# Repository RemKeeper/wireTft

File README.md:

# wireTFT

ESP32-WROOM-32D + ST7789 240×320 桌面屏。用低功耗蓝牙完成配网、换照片、切换方向和音乐摆件设置。控制页是静态 HTTPS 页面，浏览器通过 Web Bluetooth 直接连接设备，电脑上不用跑服务。每台设备有一个 6 位配置码，配置和控制都必须带上它，避免同一环境里的多块屏幕被误操作。

照片以 RGB565 保存在 SPIFFS 双槽中。整张图传输完并且 CRC 通过后才切换活动槽，所以断线、短包、CRC 错误都不会换掉上一张图。

硬件工程在 `hardware/`（KiCad 与嘉立创 EDA）。固件按 GPL-2.0 发布，见 `LICENSE`。

## 硬件连接

经典 ESP32、4 MB Flash、不需要 PSRAM。屏幕为 10 针 FPC 的 ST7789，无 MISO、无 TE。

| 信号 | GPIO |
|---|---|
| SCK | 18 |
| MOSI | 23 |
| CS | 21 |
| DC | 27 |
| RST | 33 |
| 背光 | 32，高电平点亮 |

SPI 时钟 40 MHz。这些引脚走 GPIO 矩阵，40 MHz 已是该路径的上限，不要改成 80 MHz，也超出 ST7789 的时钟规格。

## 控制页面

页面源码在 `web/public/`，用 Cloudflare Workers 的静态资源托管（`web/wrangler.jsonc`，没有 Worker 脚本）。需要桌面版 Chrome / Edge，或 Android Chrome。iOS Safari 没有 Web Bluetooth。

```text
cd web
npx wrangler deploy
```

部署完成后用自己的 `*.workers.dev` 地址打开：

1. 「搜索并连接蓝牙设备」，选择 `wireTFT-xxxx`（后 4 位是设备 ID 的末尾）。
2. 输入串口打印的 6 位配置码。勾选「记住」后，配置码按设备名存在这个浏览器的 localStorage。
3. 「02 Wi-Fi」扫描 2.4 GHz 网络并保存。
4. 「03 屏幕与画面」切换竖屏 / 横屏、发送图片、填写音乐服务地址。

照片和方向只需要蓝牙。音乐摆件需要设备已经连上 Wi-Fi。`_headers` 限制了脚本来源，并只允许本页使用蓝牙。

## 配置码

- NVS 里没有配置码时，用硬件随机数生成 6 位数字，存在键 `code`，之后重启不变。
- 每次启动串口都会打印配置码和蓝牙名称，格式为 `配置码：<六位数字>  蓝牙名称：wireTFT-xxxx`。串口输入 `code` 可再看一次，`code reset` 生成新码，浏览器里记住的旧码立即失效。
- 连续输错 5 次后，60 秒内拒绝所有要配置码的操作。蓝牙返回 `locked`，局域网返回 429。
- 蓝牙不配对、不加密。配置码只防止误操作，挡不住能听空口的人。Wi-Fi 密码也是明文经过空口，在可信环境里配网。

## 串口命令

115200 baud、8N1。打开串口会复位芯片（DTR/RTS）。

```text
wifi setup   # 交互式输入 SSID 与密码（密码不回显）
wifi status  # 连接状态与 IP
wifi forget  # 删除保存的凭据，回退到编译配置
code         # 显示配置码
code reset   # 重新生成配置码
wifi help    # 帮助
```

SSID 为 1–32 字节。密码可以为空（开放网络）、8–63 个可打印字符，或 64 位十六进制 PSK。蓝牙和串口写的是同一条 NVS 记录。没有这条记录时，使用 `idf.py menuconfig → wireTFT Wi-Fi` 里的编译配置。两项都空时不连接，等待蓝牙或串口配网。设备只支持 2.4 GHz。

没有照片时显示等待画面，底部有蓝牙名称和 Wi-Fi 状态（`WiFi OK <IP>` 等）。照片和音乐界面占满全屏。

## 构建与烧录

在 ESP-IDF 5.5 上验证。另外两个依赖要单独准备，本仓库不包含它们：

- [Arduino-ESP32 3.3.12](https://github.com/espressif/arduino-esp32/releases/tag/3.3.12)，用作 IDF 组件。`ARDUINO_COMPONENT_PATH` 指向里面的 `components/arduino`。
- [Arduino_GFX 1.6.3](https://github.com/moononournation/Arduino_GFX/releases/tag/1.6.3) 的源码目录。

这不是 Arduino IDE 工程。根 `CMakeLists.txt` 在两个路径为空时会直接失败。

```text
. $IDF_PATH/export.sh
idf.py -B build set-target esp32 \
  -DARDUINO_COMPONENT_PATH=/path/to/arduino \
  -DARDUINO_GFX_PATH=/path/to/Arduino_GFX-1.6.3
idf.py -B build menuconfig
idf.py -B build build
```

`menuconfig` 里的 `wireTFT Wi-Fi` 可以留空，以后用蓝牙或串口配置。如果在这里填了密码，它会写进构建目录的 `sdkconfig`。`sdkconfig` 已被忽略，不要提交，也不要把它和固件一起外发。

第一次烧录写入 bootloader、分区表和应用，按地址写入，不擦整片：

```text
idf.py -B build -p PORT -b 460800 flash
```

`PORT` 在 Linux 上一般是 `/dev/ttyUSB0`，Windows 上是 `COMx`。用 WSL 时，USB 串口要先接到这个发行版里。之后只改了应用：

```text
idf.py -B build -p PORT -b 460800 app-flash
```

`app-flash` 只覆盖 `0x10000` 的 factory 分区，下面这些会留下来：

| 分区 | 偏移 | 大小 | 内容 |
|---|---|---|---|
| nvs | `0x9000` | 24 KB | Wi-Fi、配置码、方向、音乐地址 |
| phy_init | `0xf000` | 4 KB | 分区表保留；本固件不往里写校准数据 |
| factory | `0x10000` | 2 MB | 应用程序 |
| images | `0x210000` | 1984 KB | 两张照片 |

不要运行 `idf.py erase-flash` 或 `esptool erase_flash`。那会清掉 NVS 和照片。也不要改 `partitions.csv` 之后再整片烧录，除非接受这些数据消失。NVS 初始化失败时固件直接停住，不会自动擦除 NVS。

烧录后用 115200 打开串口，确认打印了蓝牙名称和配置码：

```text
idf.py -B build -p PORT monitor
```

## 二次开发注意事项

### 单核

`sdkconfig.defaults` 打开了 `CONFIG_FREERTOS_UNICORE`。Wi-Fi、蓝牙控制器和 Arduino `loop` 都在 CPU0 上。不要为了“还有一个核”就关掉这个选项：Arduino loop、音乐任务和 NimBLE host 任务的亲和性、`displayLock`（屏幕）和 `musicLock`（快照）都是按单核来的。

同时固定的还有：

- `CONFIG_ESP32_REV_MIN_0`：二进制兼容 rev0 及以后。不要使用只有 rev3 才有的指令。
- `CONFIG_FREERTOS_HZ=1000`。
- Arduino loop 栈 8192 字节。音乐任务栈 8192 字节、优先级 1。NimBLE host 任务栈 6144 字节。

### Wi-Fi

固件不使用 Arduino 的 `WiFi.h`，由 `wifi_bridge.c` 直接调用 ESP-IDF 的 `esp_wifi`，只做 STA。`wifi_bridge_ap_start()` 是未接入主流程的热点辅助函数，正常启动不会开 AP。

- 凭据先用 NVS 里由蓝牙或串口写入的记录，否则用 menuconfig 的 `CONFIG_WIRETFT_SSID` / `CONFIG_WIRETFT_PASSWORD`。
- 断线后最多自动重连 5 次，用尽后要检查路由器并重启。
- HTTP 只绑在 STA 的私网 IPv4 80 端口。根 CMake 把 IDF 5.5 的 `httpd_main.c` 收成仅 IPv4，再用 `lwip_bind` 包装限制来源。不要改成监听所有地址，也不要做公网端口转发。
- `CONFIG_ESP_WIFI_STATIC_RX_BUFFER_NUM=6`，是为了给音乐模式留内部 RAM。调大就会挤占堆。
- `CONFIG_ESP_PHY_CALIBRATION_AND_DATA_STORAGE` 关闭：每次启动做完整射频校准，不把结果写入 `phy_init`。启动会稍慢，但不依赖分区里过期的校准数据。这个分区仍要留在分区表里，删掉会改变后面的偏移。

### eFuse

有的模组出厂 MAC 的 CRC 是坏的。`esp_efuse_mac_get_default()` 会得到全 0，或最低位（组播位）为 1 的地址，Wi-Fi 和蓝牙都会拒绝使用。

`wifi_bridge.c` 在协议栈启动前检查。地址无效时不烧写 eFuse，只在 RAM 里放一个本地管理地址：第一字节 `0x02`，第二字节 `0xE5`，其余字节取这次读到的 eFuse 原始值。同一块芯片每次得到同一个地址，设备 ID 保持稳定。蓝牙地址由这个基础 MAC 派生（通常加 2）。串口上的「eFuse MAC 无效，基础 MAC 使用兜底」是这条路径，不是故障。CRC 正常的模组会打印「eFuse MAC 正常」，并使用出厂地址。

不要用 `espefuse.py burn_mac` 或其它 espefuse 写命令去修 MAC。eFuse 位只能从 0 烧成 1，写错不能恢复，严重时模组无法再启动。

### 内存、分区和蓝牙

没有 PSRAM，堆都在内部 RAM。应用分区 2 MB，其中嵌入字库约 606 KB，当前固件大约占 85%。音乐模式另要约 100 KB 堆，字形缓存约 9 KB。音乐和蓝牙同时运行时，空闲堆大约 30 KB 出头，最大连续块约 27 KB。加功能之前先看这块余量。

照片分区放两个槽，每张 153600 字节加文件头。SPIFFS 只在整分区都是 `0xFF` 时格式化。已经写过的分区即使损坏也不会自动擦除。

蓝牙直接使用这份 IDF 自带的 NimBLE host，不使用 Arduino 的 BLE 库。那套库对应的 NimBLE 比 IDF 5.5 新，缺少 `ble_gap_read_local_irk`，编不过。`sdkconfig.defaults` 用选择性编译关掉了 BLE、SimpleBLE 和 BluetoothSerial。`ble_link.h` 里有强符号 `bleInUse()`，否则 Arduino 启动时会把蓝牙控制器内存释放掉。

角色只有外设，最多 1 个连接，无配对、无 GATT 客户端，首选 MTU 517。msys 和 ACL 缓冲已经减小，改回默认值会在音乐模式下把堆用完。

### 屏幕

Arduino_GFX 1.6.3 和 Arduino-ESP32 3.3.12 的 SPI 分频函数签名不一致。`components/panel/CMakeLists.txt` 只在构建目录生成兼容副本，不要改第三方库的源码。

当前没有 DMA：`writePixels()` 每批最多 32 个像素，填进 FIFO 后忙等。若要换成 ESP-IDF `spi_master`（`SPI_DMA_CH_AUTO`）或 `esp_lcd`，缓冲区必须 DMA 对齐，完成回调之后才能复用，并且不能让 Arduino 的寄存器驱动和 IDF 同时占这条总线。全屏 153600 字节在 40 MHz 下的理论下限是 30.72 ms。面板没有引出 TE，歌词区做不到与扫描同步。

## BLE 协议（protocol 2）

GATT 服务 `3f6a0001-8c2e-4d1b-9a77-5e9b1c7d0a10`：

| 特征 | UUID | 属性 |
|---|---|---|
| RX | `3f6a0002-8c2e-4d1b-9a77-5e9b1c7d0a10` | write / write without response |
| TX | `3f6a0003-8c2e-4d1b-9a77-5e9b1c7d0a10` | notify |

RX 帧首字节：`0x01` JSON 片段（未完）、`0x02` JSON 最后一片、`0x10` 图片数据（后跟 u32 小端偏移，再跟数据）。TX 帧首字节：`0x01` 应答片段（未完）、`0x02` 应答最后一片、`0x03` 事件。单条命令最长 768 字节。

每条命令为 `{"id":N,"cmd":"...","code":"123456",...}`，应答为 `{"id":N,"ok":true|false,"error":"..."}`，外加命令相关字段：

- `info`：设备 ID、蓝牙名、Wi-Fi 状态 / SSID / IP、方向、照片状态、音乐设置与状态、空闲堆。
- `wifi_scan`：异步扫描，最长 20 秒，返回去重后最多 16 个网络（`ssid`、`rssi`、`secure`）。
- `wifi_set` `{ssid, password}`、`wifi_forget`。
- `music` `{server, translation}`：`server` 为空串表示关闭。
- `display` `{orientation:"portrait"|"landscape"}`。
- `image_begin` `{orientation}`：返回 `size`（153600）、`chunk`（MTU−8，上限 500）、`window`（16384）。之后按偏移连续发送 `0x10` 帧。设备每收到 4096 字节发送 `{"evt":"image","got":N}`。客户端未确认的数据不超过 `window`。`image_end` `{crc}` 是整段载荷的标准 CRC32，通过后切换活动槽。`image_cancel` 放弃本次传输。断开连接也会放弃未完成的传输。

常见错误码：`bad_code`、`locked`（附 `retry_after` 秒数）、`bad_request`、`unknown_command`、`bad_wifi`、`scan_busy`、`bad_server`、`bad_orientation`、`image_busy`、`transfer_failed`、`crc_or_storage_error`、`save_failed`、`no_memory`。

## 局域网接口

连上 Wi-Fi 后，设备在私网地址的 80 端口提供 HTTP，并拒绝非私网来源。查询不需要配置码。写操作要带 `X-Config-Code: <配置码>`，错误返回 401，锁定返回 429。

- `GET /api/info`
- `POST /api/image`：RGB565 大端，153600 字节，头 `X-Image-CRC32`、`X-Image-Orientation`
- `POST /api/display`：`{"orientation":"portrait"|"landscape"}`
- `POST /api/music`：`{"server":"192.168.1.50:8765","translation":true}`

没有 TLS，只适合可信局域网。

## 屏幕方向

竖屏 240×320，或横屏 320×240（竖屏画面逆时针转 90°）。方向存在 NVS 键 `orient`。竖屏 MADCTL 为 `0x48`，横屏为 `0xE8`。照片槽用 magic 记下方向（`WFT1` 竖屏、`WFTL` 横屏）。换方向后，旧照片仍按原来的方向显示，需要重新发送。

## 音乐摆件

按 `lan_broadcast.md` 接入 go-musicfox：在 `config.toml` 里设置 `[main.broadcast] enable = true`，建议 `coverSize = 320`。控制页填写运行 go-musicfox 的电脑地址（私网 `IPv4:端口`，例如 `192.168.1.50:8765`）。设置存在 NVS 里，重启后自动连接。关闭后恢复照片。

- 竖屏：上方 160×160 封面，背景取封面平均色并调暗；中间一行歌名和歌手；下方歌词区延伸到底边，当前行（含翻译）居中高亮。
- 横屏：顶部整行歌名和歌手；左下 120×120 封面；右侧 182 像素宽的歌词区。
- 歌名超宽时循环滚动。当前歌词行超宽时单程滚动一次；有逐字时间时跟着演唱位置。
- SSE 和封面都是 HTTP/1.1，支持分块传输。断线 2 秒后重连，45 秒没有数据视为断开。封面只请求同一服务的 `song.coverUrl`，由 ROM 里的 TJpgDec 边收边解码，只支持基线 JPEG。
- 字库是 16 像素 GNU Unifont，由 `tools/make_lyric_font.py` 生成并嵌入（约 606 KiB，14381 字），覆盖拉丁、希腊、西里尔、日文假名、GB2312、JIS X 0208、Big5 第一级汉字和 2350 个韩文音节。
- 字库在 Flash 里线性查找一个字大约要 1.6 ms。固件把用过的字收成 16×16 的 1 位缓存（256 项），避免滚动时反复查表。
- 单条推送超过 16 KiB 会被丢掉，并报告 `event_too_large`。

实现在 `music_mode.h`（SSE、封面、渲染）和 `music_json.h`（不动态分配的 JSON 解析）。

主机端解析测试：

```text
g++ -std=c++17 -Wall -Wextra -fsanitize=address,undefined -I. tests/music_parse_test.cpp -o /tmp/music_test && /tmp/music_test
```

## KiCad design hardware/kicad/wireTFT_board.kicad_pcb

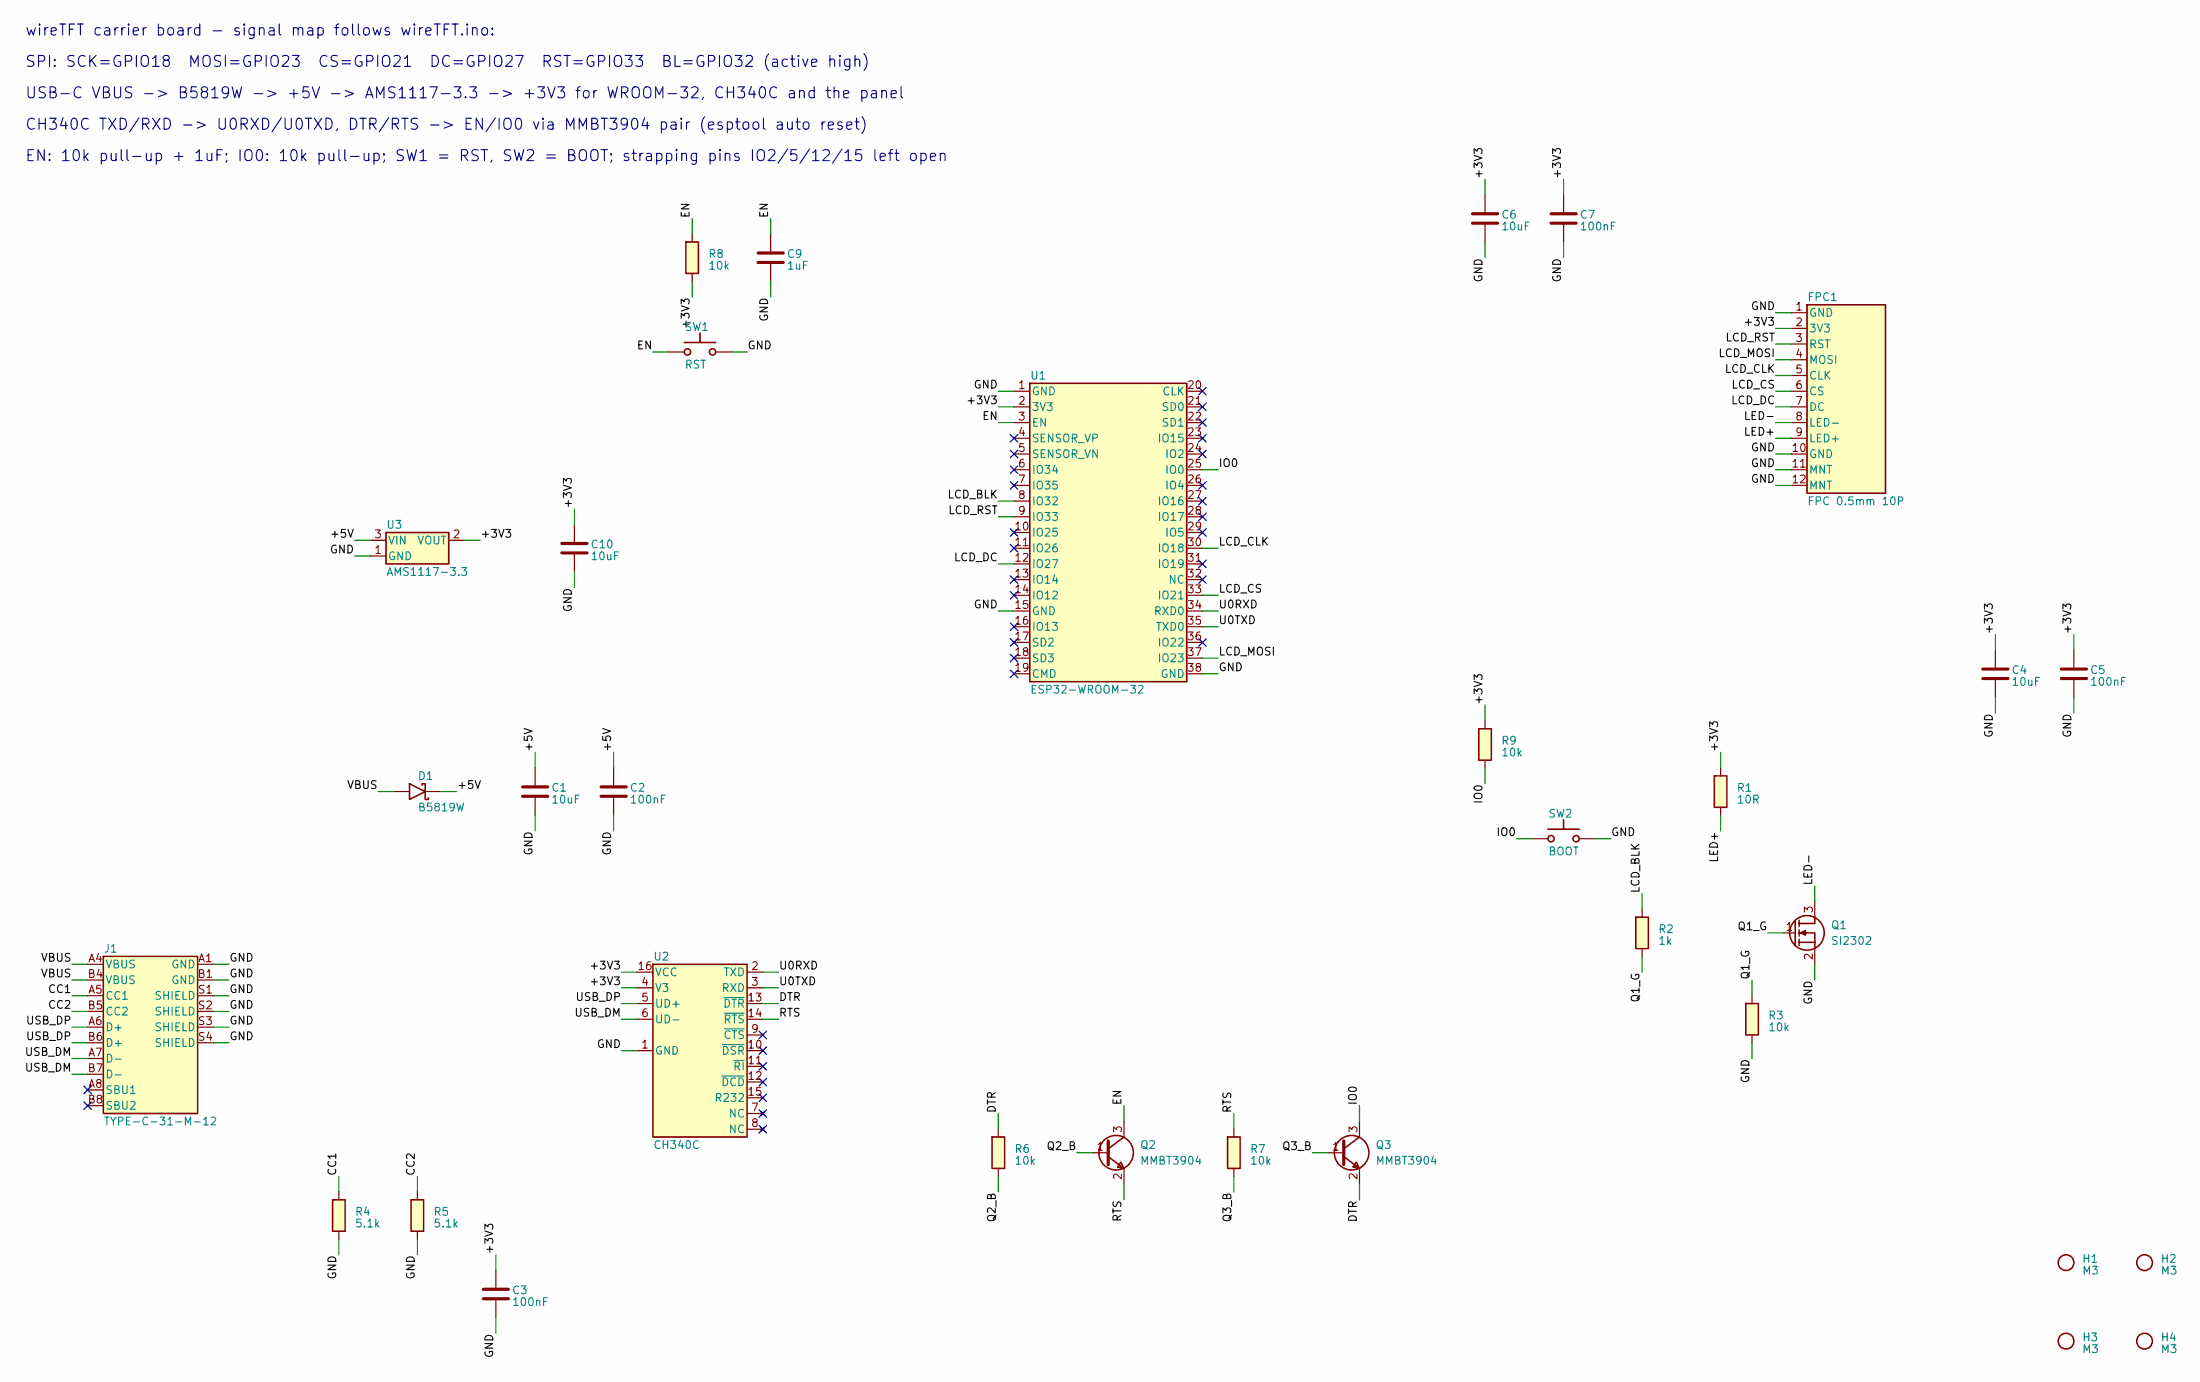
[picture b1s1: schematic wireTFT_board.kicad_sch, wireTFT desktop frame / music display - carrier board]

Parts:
C1, C4, C10: 10uF; R_0603_V; LCSC C19702
C2, C3, C5: 100nF; R_0603_V; LCSC C14663
C6: 10uF; R_0603; LCSC C19702
C7: 100nF; R_0603; LCSC C14663
C9: 1uF; R_0603; LCSC C15849
D1: B5819W; D_SOD-123_KR; LCSC C8598
FPC1: FPC 0.5mm 10P; FPC_RH24099_10P_P0.5
H1, H2, H3, H4: M3; MountingHole_3.2mm_M3
J1: TYPE-C-31-M-12; USB_C_HRO_TYPE-C-31-M-12; LCSC C165948
Q1: SI2302; SOT-23; LCSC C10487
Q2, Q3: MMBT3904; SOT-23; LCSC C20526
R1: 10R; R_0603; LCSC C22859
R2: 1k; R_0603; LCSC C21190
R3: 10k; R_0603_V; LCSC C25804
R4: 5.1k; R_0603_V; LCSC C23186
R5: 5.1k; R_0603; LCSC C23186
R6, R7, R8, R9: 10k; R_0603; LCSC C25804
SW1: RST; SW_Push_TS-1187A; LCSC C318884
SW2: BOOT; SW_Push_TS-1187A; LCSC C318884
U1: ESP32-WROOM-32; LCSC C82899
U2: CH340C; SOIC-16_H; LCSC C84681
U3: AMS1117-3.3; SOT-223-3_TabPin2; LCSC C6186

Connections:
+3V3: C3.1, C4.1, C5.1, C6.1, C7.1, C10.1, FPC1.2 (3V3), R1.1, R8.2, R9.1, U1.2 (3V3), U2.4 (V3), U2.16 (VCC), U3.2 (VOUT)
+5V: C1.1, C2.1, D1.1 (K), U3.3 (VIN)
CC1: J1.A5 (CC1), R4.1
CC2: J1.B5 (CC2), R5.1
DTR: Q3.2 (E), R6.1, U2.13 (~DTR)
EN: C9.1, Q2.3 (C), R8.1, SW1.1, U1.3 (EN)
GND: C1.2, C2.2, C3.2, C4.2, C5.2, C6.2, C7.2, C9.2, C10.2, FPC1.1 (GND), FPC1.10 (GND), FPC1.11 (MNT), FPC1.12 (MNT), J1.A1 (GND), J1.B1 (GND), J1.S1 (SHIELD), J1.S2 (SHIELD), J1.S3 (SHIELD), J1.S4 (SHIELD), Q1.2 (S), R3.2, R4.2, R5.2, SW1.2, SW2.2, U1.1 (GND), U1.15 (GND), U1.38 (GND), U2.1 (GND), U3.1 (GND)
IO0: Q3.3 (C), R9.2, SW2.1, U1.25 (IO0)
LCD_BLK: R2.1, U1.8 (IO32)
LCD_CLK: FPC1.5 (CLK), U1.30 (IO18)
LCD_CS: FPC1.6 (CS), U1.33 (IO21)
LCD_DC: FPC1.7 (DC), U1.12 (IO27)
LCD_MOSI: FPC1.4 (MOSI), U1.37 (IO23)
LCD_RST: FPC1.3 (RST), U1.9 (IO33)
LED+: FPC1.9 (LED+), R1.2
LED-: FPC1.8 (LED-), Q1.3 (D)
Q1_G: Q1.1 (G), R2.2, R3.1
Q2_B: Q2.1 (B), R6.2
Q3_B: Q3.1 (B), R7.2
RTS: Q2.2 (E), R7.1, U2.14 (~RTS)
U0RXD: U1.34 (RXD0), U2.2 (TXD)
U0TXD: U1.35 (TXD0), U2.3 (RXD)
USB_DM: J1.A7 (D-), J1.B7 (D-), U2.6 (UD-)
USB_DP: J1.A6 (D+), J1.B6 (D+), U2.5 (UD+)
VBUS: D1.2 (A), J1.A4 (VBUS), J1.B4 (VBUS)

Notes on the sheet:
wireTFT carrier board - signal map follows wireTFT.ino:
SPI: SCK=GPIO18 MOSI=GPIO23 CS=GPIO21 DC=GPIO27 RST=GPIO33 BL=GPIO32 (active high)
USB-C VBUS -> B5819W -> +5V -> AMS1117-3.3 -> +3V3 for WROOM-32, CH340C and the panel
CH340C TXD/RXD -> U0RXD/U0TXD, DTR/RTS -> EN/IO0 via MMBT3904 pair (esptool auto reset)
EN: 10k pull-up + 1uF; IO0: 10k pull-up; SW1 = RST, SW2 = BOOT; strapping pins IO2/5/12/15 left open

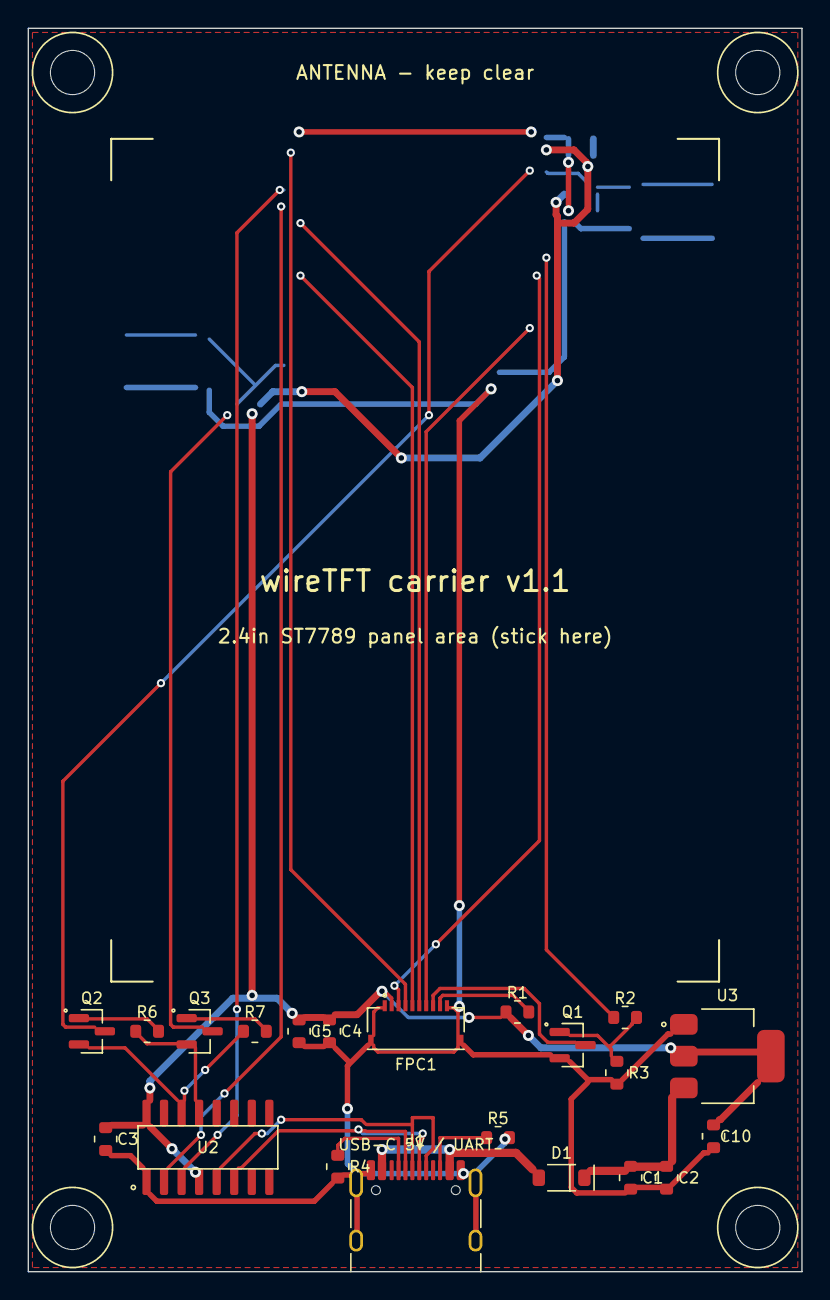
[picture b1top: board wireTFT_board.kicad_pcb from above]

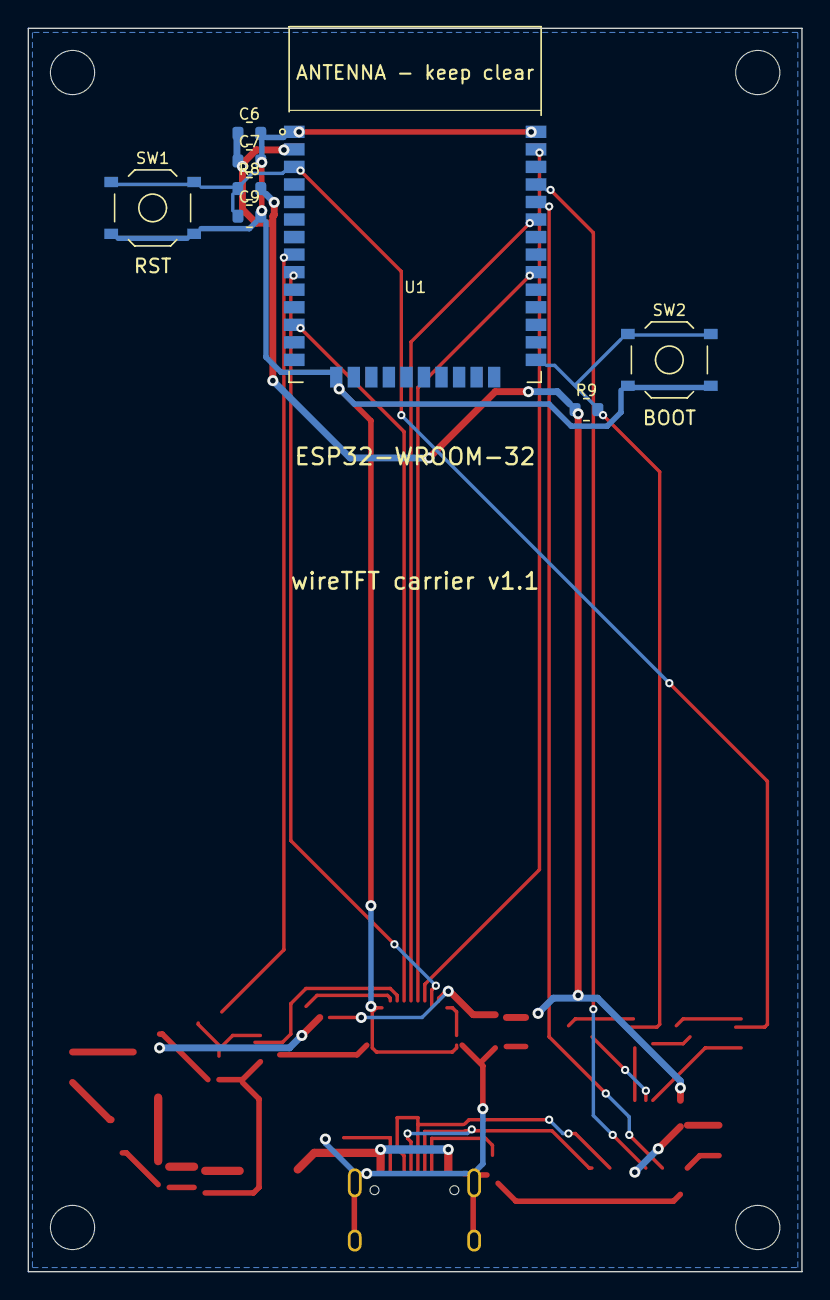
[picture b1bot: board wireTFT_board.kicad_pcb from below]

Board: 2 copper layers, 56.0 x 90.0 mm, 33 parts (8 on the bottom side), 25 nets.

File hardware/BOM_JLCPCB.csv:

Comment,Designator,Footprint,JLCPCB Part #,Quantity,Note
10uF,"C1,C10,C4",R_0603_V,C19702,3,
100nF,"C2,C3,C5",R_0603_V,C14663,3,
10uF,C6,R_0603,C19702,1,
100nF,C7,R_0603,C14663,1,
1uF,C9,R_0603,C15849,1,
B5819W,D1,D_SOD-123_KR,C8598,1,
FPC 0.5-10P HYH2.0,FPC1,FPC-SMD_10P-P0.50_FPC-0.5-10P-HYH2.0,C6364659,1,"SHOU HAN 0.5mm 10P flip-top, double-sided (top+bottom) contacts, H2.0; panel FPC folds behind the screen, pin order mirrored"
TYPE-C-31-M-12,J1,USB_C_HRO_TYPE-C-31-M-12,C165948,1,
SI2302,Q1,SOT-23,C10487,1,
MMBT3904,"Q2,Q3",SOT-23,C20526,2,
10R,R1,R_0603,C22859,1,
1k,R2,R_0603,C21190,1,
10k,R3,R_0603_V,C25804,1,
5.1k,R4,R_0603_V,C23186,1,
5.1k,R5,R_0603,C23186,1,
10k,"R6,R7,R8,R9",R_0603,C25804,4,
RST,SW1,SW_Push_TS-1187A,C318884,1,
BOOT,SW2,SW_Push_TS-1187A,C318884,1,
ESP32-WROOM-32,U1,ESP32-WROOM-32,C82899,1,"ESP32-WROOM-32 (4MB), soldered on the back, antenna at the top edge"
CH340C,U2,SOIC-16_H,C84681,1,
AMS1117-3.3,U3,SOT-223-3_TabPin2,C6186,1,
